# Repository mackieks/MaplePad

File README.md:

# MaplePad🍁<br/>

MaplePad is an all-in-one Dreamcast controller, VMU, and Purupuru (rumble pack) emulator for Dreamcast portables and custom Dreamcast controllers. It runs on RP2040 and is usable with the Raspberry Pi Pico as well as custom MaplePad PCBs. See the [hardware folder](https://github.com/mackieks/MaplePad/tree/main/hardware) for a wiring diagram.

**Note:** MaplePad is still a WIP. You may experience issues with [Windows CE games](https://segaretro.org/Windows_CE). In almost all problematic titles, disabling VMU and rumble through the MaplePad menu will make the game playable. Check out the [Compatibility List](https://docs.google.com/spreadsheets/d/1JzTGN29Ci8SeuSGkQHLN1p6ayQNWUcsNw77SMujkjbs/edit?usp=sharing) for details!

## Features
With MaplePad you can cycle through 8 200-block internal VMUs with custom icons and colors, use an I2C or SPI OLED display to see the VMU screen in color and at 2x integer scale, and enjoy rumble that is 1:1 with the Performance TremorPak in most retail software (still some minor bugs!)

### Feature List:
- [x] Full FT<sub>0</sub> (controller) support including analog joystick and triggers
- [x] Full FT<sub>1</sub> (storage) support for savegames with 1600 blocks of space
- [x] Multipaging for memory card (8 separate 200-block memory cards)
- [x] Full FT<sub>2</sub> (LCD) support with SSD1331 96\*64 color SPI OLED for VMU display (monochrome SSD1306 128\*64 I2C OLED also supported)
- [x] Customizable color palettes for all 8 internal memory cards
- [x] Robust FT<sub>8</sub> (vibration) functionality (WIP)
- [x] Robust FT<sub>3</sub> (timer/RTC) reporting for compatibility purposes (no RTC)
- [x] Basic menu on SSD1306 and SSD1331 OLED for configuring MaplePad behavior (WIP)

### To-do: 
Release v1.6 is gated by the following TODOs
- [ ] Finish menu (button test, VMU palette editor, misc. bugs)
- [ ] Address issues with non-CE games (Crazy Taxi, Blue Stinger, Powerstone 2)
- [ ] Finish FT<sub>8</sub> (vibration) continuous vibration and AST

Future TODOs
- [ ] Fix compatibility with Windows CE games
- [ ] Implement 'fancy' VMU color palettes (gradients, animated backgrounds, etc.)
- [ ] Implement option for DC boot animation on OLED
- [ ] Add external RTC for true FT<sub>3</sub> (timer/RTC) support
- [ ] Implement FT<sub>4</sub> (microphone) support

## Project Showcase
*StrikerDC MaplePad mod by Wesk*

*MaplePad Arcade Controller with VMU de GamesCare. [link](https://gamescare.com.br/produto/controle-arcade-dreamcast-tela-de-vmu-e-8-vmus-virtuais-na-placa-maple-board/), [video](https://www.youtube.com/watch?v=b0IbSASR3B4/)*

*Mini Arcade Stick de Mundo Yakara Colombia. Excellent video that showcases MaplePad v1.5 features! [video](https://www.youtube.com/watch?v=jbHO3rEyzZU)*

*Mini plug'n'play virtual memory card by jounge. [link](https://tieba.baidu.com/p/8465994390)*

*Various JAMMA Dreamcast adapters available on AliExpress. [link 1](https://www.aliexpress.us/item/3256805216279752.html), [link 2](https://www.aliexpress.us/item/3256804674679708.html), [video](https://www.youtube.com/shorts/UciW3vM-KWo) (flashing lights warning!)*

*Giant Dreamcast VMU + Arcade Stick by CrazyJojo (code modified). [video](https://www.youtube.com/watch?v=bEA_On7P_g8)*

## Dumping VMUs to PC
You can use [picotool](https://github.com/raspberrypi/picotool) to dump VMUs manually. Here's the process:

- Put RP2040 into programming mode with BOOTSEL button and connect it to your PC
- Use picotool to dump whichever VMU page you want: `picotool save -r 10020000 10040000 dump1.bin`

- VMUs start at 0x10020000 and each one is 0x20000 long. So to save page 7, for example, you'd use 
`picotool save -r 100E0000 10100000 dump7.bin`
- Open dump in [VMU Explorer](https://segaretro.org/VMU_Explorer)

## License
<br />This work is licensed under a <a rel="license" href="http://creativecommons.org/licenses/by/4.0/">Creative Commons Attribution 4.0 International License</a>.

Share — copy and redistribute the material in any medium or format <br />
Adapt — remix, transform, and build upon the material for any purpose, even commercially. <br />
Attribution — You must give appropriate credit, provide a link to the license, and indicate if changes were made. <br />

MaplePad is forked from [Charlie Cole's Pop'n Music Controller.](https://github.com/charcole/Dreamcast-PopnMusic)

Special thanks: [Charlie Cole](https://github.com/charcole), [Colton Pawielski](https://github.com/cepawiel) and [Wesk](https://www.youtube.com/channel/UCYAwbbBxi5_LK8WVrD10SUw).

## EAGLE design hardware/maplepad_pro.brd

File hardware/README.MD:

# Raspberry Pi Pico

Wiring diagram for Raspberry Pi Pico: 

Notes:
- Do not connect a USB cable to the Pico when it is connected to the Dreamcast. (5V will backfeed to console!)
- The official Raspberry Pi Pico must be modded to access the right trigger pin (ADC3). See the wiring diagram for details.
- For rumble, use an N-channel FET with V<sub>GS(th)</sub> < 3V and I<sub>d</sub> ≥ 1A. Both large Xbox-style ERMs and coin-type vibration motors work well.
- You can add a freewheel diode between 5V and the NFET's drain if you'd like, but it's not necessary for prototyping.
- Connect OLED_SEL to GND to select the SSD1306 OLED. Leave floating to select the SSD1331 OLED.
- When wiring the SSD1306 I2C OLED, SDA and SCL need to be swapped and will not match the silkscreen on the OLED PCB. See the wiring diagram for details.
- The SSD1331 SPI OLED runs at a high clock speed. Use at least 34AWG wire and keep the wires short and direct.

# MaplePad 

Replacement Dreamcast controller PCB for portablizing, using RP2040. EAGLE source, Gerbers, BOM and assembly drawing are available in this directory. (Photo below is of the previous revision which lacked the BOOTSEL button.)

Recommended board fabrication specs: 
- 0.8mm 2-layer PCB
- ENIG (for chipscale BGAs)
- Red soldermask - optional, but in keeping with the Japanese maple theme :) 

JLCPCB may grow the drills under the flash to meet their spec-- this is OK. Also please note that the extremely small castellations often result in many 'crushed barrels' that require manual cleanup.

Features:
- [x] 18.5 x 22.4mm 2-layer PCB
- [x] USB-C and BOOTSEL button for programming
- [x] Full Dreamcast controller compatibility
- [x] Analog joystick and triggers
- [x] VMU emulation (8-page VMU, 1600 blocks total)
- [x] SPI/I2C OLED for VMU screen
- [x] Rumble (Purupuru) support (WIP)
- [x] Power from 1.8V - 5.5V

What it doesn't support:
- [ ] Dual analog sticks
- [ ] Dreamcast Microphone
- [ ] Dreamcast Keyboard, Mouse, or Fishing Controller

A future version may support these features.

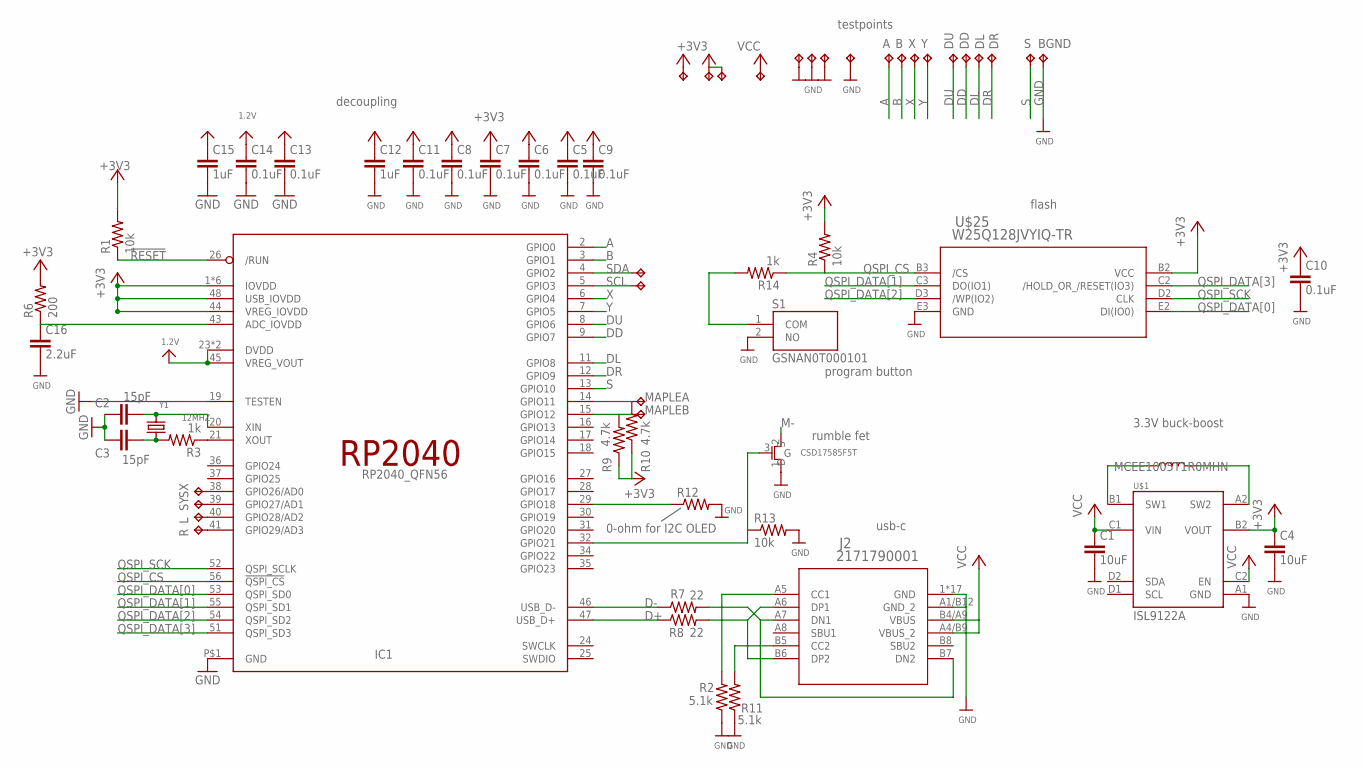
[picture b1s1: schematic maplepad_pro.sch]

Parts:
A, A0: TPTP10R; TP10R
B, B0: TPTP10R; TP10R
BGND: TPTP10R; TP10R
C1, C4: 10uF; C0402
C2, C3: 15pF; C0201
C5, C6, C7, C8, C9, C10, C11, C13, C14: 0.1uF; C0201
C12, C15: 1uF; C0402
C16: 2.2uF; C0402
DD: TPTP10R; TP10R
DL: TPTP10R; TP10R
DR: TPTP10R; TP10R
DU: TPTP10R; TP10R
IC1: RP2040_QFN56; QFN56_7MM_REDUCEDEPAD
J2: 2171790001; 2171790001_MOL
L: TPTP10R; TP10R
L2: MCEE1005T1R0MHN; R0402
LR3.1, LR3.3: TPTP10R; TP10R
LRGND, LRGND1: TPTP10R; TP10R
R: TPTP10R; TP10R
R1, R4, R13: 10k; R0201
R2, R11: 5.1k; R0201
R3, R14: 1k; R0201
R6: 200; R0201
R7, R8: 22; R0201
R9, R10: 4.7k; R0201
R12: 0-ohm for I2C OLED; R0201
S, S3.3: TPTP10R; TP10R
S1: GSNAN0T000101
SCL: TPTP10R; TP10R
SDA: TPTP10R; TP10R
SGND: TPTP10R; TP10R
SX: TPTP10R; TP10R
SY: TPTP10R; TP10R
U1: CSD17585F5T; YJK3_TEX
U$1: ISL9122A
U$25: W25Q128JVYIQ-TR; WLCSP24
V3.3: TPTP10R; TP10R
VGND: TPTP10R; TP10R
X: TPTP10R; TP10R
Y: TPTP10R; TP10R
Y1: 12MHZ; CRYSTAL_2.5X2

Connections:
1.2V: C13.1, C14.1, C15.1, IC1.23 (DVDD), IC1.45 (VREG_VOUT), IC1.50 (DVDD)
!RESET: IC1.26 (/RUN), R1.1
+3V3: C4.1, C5.1, C6.1, C7.1, C8.1, C9.1, C10.1, C11.1, C12.1, IC1.1 (IOVDD), IC1.10 (IOVDD), IC1.22 (IOVDD), IC1.33 (IOVDD), IC1.42 (IOVDD), IC1.44 (VREG_IOVDD), IC1.48 (USB_IOVDD), IC1.49 (IOVDD), LR3.3.TP, R1.2, R4.2, R6.2, R9.1, R10.1, S3.3.TP, U$1.B2 (VOUT), U$25.B2 (VCC), V3.3.TP
A: A.TP, IC1.2 (GPIO0)
B: B.TP, IC1.3 (GPIO1)
D+: IC1.47 (USB_D+), R8.1
D-: IC1.46 (USB_D-), R7.1
DD: DD.TP, IC1.9 (GPIO7)
DL: DL.TP, IC1.11 (GPIO8)
DR: DR.TP, IC1.12 (GPIO9)
DU: DU.TP, IC1.8 (GPIO6)
GND: BGND.TP, C1.2, C2.1, C3.1, C4.2, C5.2, C6.2, C7.2, C8.2, C9.2, C10.2, C11.2, C12.2, C13.2, C14.2, C15.2, C16.2, IC1.19 (TESTEN), IC1.P$1 (GND), J2.1 (GND), J2.2 (GND), J2.3 (GND), J2.4 (GND), J2.13 (GND), J2.14 (GND), J2.15 (GND), J2.16 (GND), J2.A1/B12 (GND_2), J2.B1/A12 (GND), J2.S_1_H1 (GND), J2.S_1_H2 (GND), J2.S_2_H1 (GND), J2.S_2_H2 (GND), J2.S_3_H1 (GND), J2.S_3_H2 (GND), J2.S_4_H1 (GND), J2.S_4_H2 (GND), LRGND.TP, LRGND1.TP, R2.1, R11.1, R12.2, R13.2, S1.2 (NO), SGND.TP, U1.1 (S), U$1.A1 (GND), U$25.E3 (GND), VGND.TP
M-: U1.2 (D)
MAPLEA: A0.TP, IC1.14 (GPIO11), R10.2
MAPLEB: B0.TP, IC1.15 (GPIO12), R9.2
unnamed: IC1.41 (GPIO29/AD3), R.TP
unnamed: IC1.40 (GPIO28/AD2), L.TP
unnamed: L2.1, U$1.B1 (SW1)
unnamed: L2.2, U$1.A2 (SW2)
unnamed: C2.2, IC1.20 (XIN), Y1.3 (2)
unnamed: C3.2, R3.2, Y1.1
unnamed: IC1.21 (XOUT), R3.1
unnamed: R14.2, S1.1 (COM)
unnamed: C16.1, IC1.43 (ADC_IOVDD), R6.1
unnamed: J2.A7 (DN1), J2.B7 (DN2), R7.2
unnamed: J2.A6 (DP1), J2.B6 (DP2), R8.2
unnamed: IC1.39 (GPIO27/AD1), SY.TP
unnamed: IC1.38 (GPIO26/AD0), SX.TP
unnamed: IC1.29 (GPIO18), R12.1
unnamed: J2.B5 (CC2), R11.2
unnamed: J2.A5 (CC1), R2.2
unnamed: IC1.32 (GPIO21), R13.1, U1.3 (G)
QSPI_CS: IC1.56 (!QSPI_CS), R4.1, R14.1, U$25.B3 (/CS)
QSPI_DATA[0]: IC1.53 (QSPI_SD0), U$25.E2 (DI(IO0))
QSPI_DATA[1]: IC1.55 (QSPI_SD1), U$25.C3 (DO(IO1))
QSPI_DATA[2]: IC1.54 (QSPI_SD2), U$25.D3 (/WP(IO2))
QSPI_DATA[3]: IC1.51 (QSPI_SD3), U$25.C2 (/HOLD_OR_/RESET(IO3))
QSPI_SCK: IC1.52 (QSPI_SCLK), U$25.D2 (CLK)
S: IC1.13 (GPIO10), S.TP
SCL: IC1.5 (GPIO3), SCL.TP
SDA: IC1.4 (GPIO2), SDA.TP
VCC: C1.1, J2.A4/B9 (VBUS_2), J2.B4/A9 (VBUS), LR3.1.TP, U$1.C1 (VIN), U$1.C2 (EN)
X: IC1.6 (GPIO4), X.TP
Y: IC1.7 (GPIO5), Y.TP

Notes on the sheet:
MCEE1005T1R0MHN
ISL9122A
3.3V buck-boost
flash
usb-c
rumble fet
testpoints
decoupling
program button

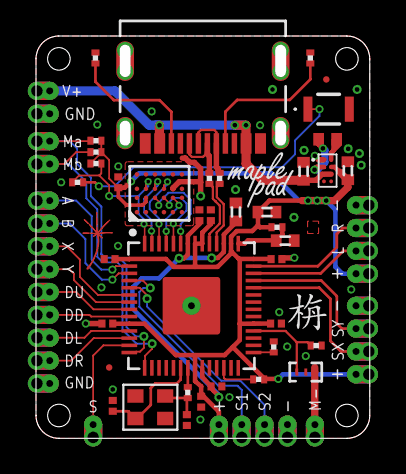
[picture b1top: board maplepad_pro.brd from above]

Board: 2 copper layers, 17.9 x 21.7 mm, 63 parts (0 on the bottom side), 43 nets.

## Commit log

2021-01-31 Working Maple input
2021-02-01 Working controller emulation
2021-02-07 Buttons and LEDs but bad packets are back
2021-02-07 PIO code golf
2021-02-12 New faster decoding (untested)
2021-02-12 Cache built packets for faster sending
2021-02-13 Some fast recieve bug fixing
2021-02-13 Working!
2021-02-13 Removed unused code now working
2021-02-14 Tidied up and commented ready for release
2021-02-14 Moved state machine into own file
2021-02-14 Comment and tidy ready for release
2021-02-14 Fixed typo
2021-02-14 Far too long README that no-one will ever read
2021-02-14 Add VSCode config files
2021-02-14 Added photos and design files
2021-02-14 Added link to photos and fixed some errors
2021-02-14 Added license
2021-02-14 Improved README
2021-02-14 Tweaked README
2021-02-14 Added Fusion 360 screenshot
2021-02-16 Fixed typos
2021-02-21 Initialize TXDMAChannel properly
2021-02-27 Memory card support
2021-02-28 Working memory card support
2021-02-28 Commented odd behaviour
2021-02-28 Memory card fixes
2021-03-02 Preformat memory card with custom icon
2021-03-02 Update flash offset to force reformat of memory card
2021-03-02 Add more information about memory card functionality
2021-03-06 Support being plugged in on any port
2021-03-06 First attempt at controller board that fits in PCB slot
2021-03-06 Added 5V LED drivers
2021-03-20 Switched misleading silkscreen and updated part numbers
2021-03-20 Added some info about PCB
2021-08-19 Addition of analog stick
2021-08-30 FT2: I2C LCD
    Added:
    -Monochrome LCD (FT2) with SSD1306 128*64 I2C OLED for VMU display
    -Analog Triggers
    -Basic Timer (FT3) reporting; Timer packets not yet implemented
2021-09-04 MaplePad Hardware Update
    -Updated pin assignments in maple.c for MaplePad
    -Gerbers and BOM for MaplePad PCB added
    -Preliminary dual subperipheral support added
    -Preliminary FT8 (vibration) packet format
2021-09-04 Rename Hardware.MD to README.MD
2021-09-05 Multipaging Update
    -Added multipaging to FT1 Storage functionality
    -8 separate 200-block memory cards
    -Interrupt-driven page cycling using pushbutton
    Misc:
    -Toned down overclock to mitigate instability (now 200MHz)
2021-09-05 Page Button Fix
    -Added 750ms page cycle debounce delay
    -Initial support for 128*64 OLED testing
2021-11-20 spi color oled in progress
2021-11-21 Custom palettes for SPI OLED
2022-02-01 WIP Rumble Implementation
    -Purupuru functionality (WIP)
    -Color SPI OLED tweaks
    ...and probably more I've forgotten!
2022-07-12 Initial Purupuru Support
    Added basic vibe handling code. Still many many things to implement
2022-07-12 Add MaplePad PCB image
2022-07-12 MaplePad HW Files
    -EAGLE schematic and board
    -Gerbers
    -BOM
    -Assembly drawing
2022-07-12 Add maplepad_pcb.jpg
2022-07-12 Update HW stuff
2022-07-12 Add maplepad_logo.png
2022-07-15 Fix profile.gbr
2022-07-15 working on Pico/MaplePad support
2022-07-15 Rename Icon/Icon.c to icon/Icon.c
2022-07-15 Revert "Rename Icon/Icon.c to icon/Icon.c"
    This reverts commit 7aa6d986047386498e97657ecb66427d15105bdc.
2022-07-15 Working on HKT-7300 support
2022-07-17 Fix format.c
2022-07-17 Remove build/
2022-07-20 vibeHandler floats
2022-07-28 Purupuru Updates
    -Basic and incremented purupuru pulses working
    -New logo
2022-07-31 PuruPuru and FT2 DMA Update
    Massive update:
    -Vibration handling is almost feature-complete, including incrementing pulses, convergent and divergent vibration, and auto-stop time framework.
    -SSD1331 OLED now uses DMA instead of blocking SPI
    -Optional button combo (X + Y + Start) to activate VMU page cycle
    -Tweaks to rumble GPIO settings
2022-08-04 Memory card format and rumble hotfix
2022-08-08 VMU improvements, rumble fixes, bug squashin'
    -Filesystem tweaks to increase data area to 238 blocks per page
    -Rate-limited button combo VMU page cycling
    -Fixed vibeHandler timer settings to improve accuracy
    -Fixed incorrect handling of Purupuru commands when vibePower = 0
    -Increased flash_write_delay to improve reliability
    -Custom palettes in Dreamcast BIOS for memory cards
2022-08-15 Packet format updates
    Various bugfixes for issues found while troubleshooting Sega Rally 2, mostly packet formatting stuff
    Revert to 200 block memcards to avoid issues when copying in BIOS
2022-08-16 WIP stuff
    -forward and backward vmu cycling
    -persistent vmu pages
2022-08-18 menu updates
2022-08-18 FT3 Timer Initial Support
    ft3 data structures, command handling, block_read bugfixes
2022-09-19 Menu updates, packet data fixes, cleanup
2022-09-19 remove stdio_usb (oops)
2022-09-19 rearrange images
2022-09-19 add strikerDC images
2022-09-30 added wiring diagram!
2022-10-16 Fix Extended Device Info fields
    -fixed arcade stick free device status
    -fixed arcade stick power consumption
    -updated standard controller free device status to more recent HKT-7700 revision
2022-10-19 move drawing funcs to draw.c
    Prep for bringing back full ssd1306 support (menu+vmu)
2022-10-20 display.c
    reorganizing
2022-10-20 move LICENSE
2022-10-20 oledType fixes
    mono OLED fixes (WIP)
2022-10-21 SSD1306 OLED Support
    Monochrome I2C SSD1306 OLED support now working! Also you can swap L&R triggers or X&Y axes in the menu now.
    plus some random bugfixes for the menu flags
2022-10-21 Update LICENSE
2022-12-10 1.4d update
2023-01-09 Update maple.c
    Fix firstboot vmu formatting issue
2023-02-21 Working on menu + new stick config
2023-02-23 Ellipse fill and button test screen
2023-02-23 tweaking stick deadzone/calib stuff
2023-02-23 Working on antideadzone
2023-04-05 Update maple.c
    reverting WIP antideadzone stuff; more important stuff to work on right now
2023-04-13 revert old wip stuff
2023-04-14 update sCal, iconData
    -fix stick calibration wizard
    -remove extra icon data
2023-04-14 wip stuff
    -trying to remove outer stick deadzone
    -working on hiding menu entries for ssd1306
2023-04-14 deadzone work
    -tweaked stick/trigger calibration
    -working on deadzone adjustment menus
2023-04-14 formatting
2023-04-15 update menu, scal/tcal
    -remove janky entry hiding
    -implement deadzone adjust menus for stick/triggers
    -formatting
2023-11-29 arcade soft reset wip
    working on new lcd support, soft reset for arcade cab
2023-12-04 maplepad v1.5
    -hugely improved stick calibration (fully automatic)
    -deadzone and anti-deadzone adjustment for stick and triggers
    -autoreset with configurable timer and inter-maplepad communication for arcade cabinets
    -optimized display pixel-setting functions (reduces controller disconnects during saving)
    -fixed ssd1306 clearDisplay bug
    -added Settings menu controller type indicator
2024-01-23 Create HW_LICENSE.txt
    solderpad license for hw
2024-11-11 init check-in, staging for refactoring
2024-11-12 added gpios and changed maplebus pins
2024-11-13 setup callback for vmu to only update flash when storage is written to
2024-11-15 removing remnants of usb now that I understand how the communications work. TODO update IO within DreamcastController
2024-11-15 missed removing a subdirectory
2024-11-15 implemented gpio for button presses and injected it into the DreamcastController handlePacket() method
2024-11-16 removing checked in build cache files
2024-11-16 fixed compiler issues
2024-11-20 Added adc reads for trigger + joystick inputs
2024-11-20 organizing for screen implementation
2024-11-20 added to cmake before I forget
2024-11-21 configured oled 1331 and displayed splashscreen
2024-11-25 enabling uart for debugging
2024-11-26 screen now updates with maple packets, need to fix display rendering
2024-11-28 fixed screen artifacting and added 2x integer scaling. this code is tech debt and is in desperate need of refactoring/optimization
2024-11-28 some code cleanup
2024-11-28 figure out why the pointer to lcd is too slow an causing the controller to pause
2024-11-29 improved lcd implementation for performance
2024-11-30 resolved screen update issues
2024-11-30 small optimization
2024-12-01 please don't judge me for the poor font implementation
2024-12-02 cleaned up fonts
2024-12-02 beginning to integrate menu system
2024-12-06 setup framework for menu system
2024-12-11 updated to 2.1 pico sdk
2024-12-12 updated menu with cursor and scrolling
2024-12-12 some refactoring
2024-12-13 menu improvements
2024-12-14 updates to how memory is handled to allow for paging
2024-12-17 push everything
2024-12-17 fix for oled sel
2024-12-18 cleaned up paging and stabilized it
2024-12-18 some minor refactoring for paging
2024-12-18 added logic to detect uart to swap A and B buttons
2024-12-29 minor refactoring and plumbing for observers
2024-12-30 observer pattern is 'working'
2025-01-02 these changes are going to be reverted
2025-01-02 reverting to previous commit
2025-01-02 resolved previous commit issues where screen logic was too slow causing the controller to crash
2025-01-03 need to figure out how to save memory for buffers
2025-01-07 Added logic to handle an overlay that appears for 2 seconds then goes back to displaying content on the screen
2025-01-08 modified the overlay so that it only takes a portion of the top screen, leaving the rest of the content to be rendered as normal
2025-01-10 lots of overlay updates
2025-01-10 addressed oom issues, probably created more headaches for future me
2025-01-11 extreme hoarders, static variable cleanup edition
2025-01-12 It pains me to have to implement fonts this way, but hashtables were proving to be too hard on memory
2025-01-14 fully expecting to have to revert back to a previous commit with these changes.
2025-01-15 these changes will be reverted
2025-01-15 Revert "these changes will be reverted"
    This reverts commit 13d6e20f658a472039c56de2295e74f7eeeab584.
2025-01-15 Revert "fully expecting to have to revert back to a previous commit with these changes."
    This reverts commit f9f0f88d52b299bf84395fcb49b3441ae3920cd0.
2025-01-15 Revert "It pains me to have to implement fonts this way, but hashtables were proving to be too hard on memory"
    This reverts commit cd45ddc3e47e3ec0241de3ceff5dc994dd6091fc.
2025-01-15 reverted changes
2025-01-15 changed compile settings to run Os (size) optimization to fix memory issues, thanks Tails!
2025-01-16 Broke menu out into it's own subdirectory
2025-01-29 implemented reading flash for storing settings data, next up storing it
2025-01-31 settings saving, will do some refactoring to make it cleaner
2025-01-31 oops, forgot to cleanup some stuff before committing
2025-01-31 happier with this memory approach to saving settings data
2025-02-01 more menu work, it's getting there!
2025-02-03 settings persisting and startup check created to set defaults when firmware is upgraded
2025-02-04 controller now uses configurations updated in settings
2025-02-04 bug squishing
2025-02-05 resolved a lot of issues
2025-02-05 more bug fixes
2025-02-06 removed need for pulling in sdk as submodule, pico sdk should now be cloned locally from the master branch
2025-02-07 updated for Pico2
2025-03-08 Rename 主机演示2[00_05_12][20221030-111434].png to jojo1
2025-03-08 Rename jojo1 to jojo1.png
2025-03-08 Rename images/从机演示2生化[00_08_05][20221030-111628].png to jojo2.png
2025-03-08 Rename 从机演示4[00_01_19][20221030-111601].png to jojo3.png
2025-03-08 Rename jojo2.png to images/jojo2.png

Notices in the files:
parts and their libraries:
microbuilder: This work is placed in the public domain, and may be freely used for commercial and non-commercial work with the following conditions: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
personal: COPYRIGHT: Copyright (C) 2022 Ultra Librarian. All rights reserved.
COPYRIGHT: Copyright (C) 2018 Accelerated Designs. All rights reserved
